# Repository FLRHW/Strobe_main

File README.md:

<h1 align="center">Main board</h1>

<p align="center" width="100%">
  
</p>

***

<p align="center">
  
&nbsp; &nbsp; &nbsp; &nbsp;
  
</p>

***

# **1 kV strobe - Intro**
Since my teenage years I spend a great chunk of my spare time on hobby electronics. Back then, much of that time was to build FM transmitters, audio amplifiers and strobe lights. I was always pushing my builds as much as I could, (i.e., extracting pressurised smoke from capacitors!) as an attempt to make the flashes ever brighter. It was somewhat challenging given the limited experience and resources I had at the time, but a lot of fun nonetheless.
Life went on, priorities changed and for a long time I did not "play" with strobe lights... until recently, after I saw a large XOP-15 bulb for sale and, well, nostalgy happened.

While defining the project scope, I had to decide if I'd use the good old Xenon bulb or move to LEDs, as these have greatly evolved and are ubiquitous nowadays, making their way to commercial strobes (https://www.martin.com/en/products/atomic-3000-led). I have decided to stick to vintage tech, as in my mind this would bring more interesting power electronics challenges due to high voltages and high peak currents required when the lamp is ionised.

So that's what this repo contains: a Xenon-based strobe light, aiming to drive a XOP-15 bulb with up to 1 kV, while controlling the duration and frequency of pulses.

## Project overview
This repository contains KiCad v9 design files for the main board of a Xenon-based strobe light system.
The system is divided into three separate modules:

- Main board. This board drives the Xenon bulb, generating the trigger pulse and actively interrupting the discharge according to the required pulse width. The latest STM32 source code is kept on a separate repository:  
https://github.com/FLRHW/Strobe_main_source  

- HMI board. This is the user interface, to capture desired operating conditions (bus voltage, pulse width and pulse frequency). That board is covered on a separate repository:  
https://github.com/FLRHW/Strobe_HMI  

- Power supply. This is to produce an adjustable DC supply and to realise that I intend to eventually design an AC-mains powered converter, including a PFC circuit. As an interim solution, off-the-shelf boost converter modules are used: two such modules are connected in series, each providing up to 450 V output while supplied by 12 V batteries. As a side project, the boost modules have been reverse engineered with the aim to modify them from non-isolated to isolated. This work is covered under the following repos:
https://github.com/FLRHW/StepUp_module_12to450V  
https://github.com/FLRHW/Isolated_12to450V.

## Design targets
DC bus voltage: 400 V to 1000 V  
Flash rate: 0.1 Hz to 200 Hz  
Pulse duration: 20 μs to 10 ms  

Please note that the above parameters are only the limits encoded in the software. This design relies on storing energy on a capacitor bank to then discharge it into the bulb, so, even though the limit in software for the pulse duration is 50 % of the period, long durations might be unachievable. The duration strongly depends on the lamp, capacitor bank and bus voltage. As an example, with the XOP-15 and a 400 uF bank charged to 700 V, the discharge current reaches 450 A and the bank voltage collapses in less than 1 ms. Additionally, the HV power supply will determine how fast the capacitor bank is recharged, limiting the flash rate and/or pulse duration.

## Intended use
This repository is intended for:
* Educational use and study of the circuit;
* Integration into hobby or research projects.

## License
The design files and documentation in this repository are released under the CERN Open Hardware Licence v2 – Permissive (CERN‑OHL‑P‑2.0). SPDX identifier: CERN-OHL-P-2.0 See the LICENSE file for the full legal text and conditions.
In short and non‑legal terms, you are free to use, modify, manufacture, and distribute hardware based on these files, provided you respect attribution requirements and the terms in the license.

## Trademarks and third‑party rights
All product names, logos, and brands eventually mentioned are the property of their respective owners and are not included or licensed here.
Any reference to third‑party marks is purely descriptive and does not imply endorsement or affiliation.

## Safety and disclaimer
* The author takes no responsibility for any injury, death or damage arising from the use, direct or indirect, of the design or otherwise any information from this repository
* You shall not build this or any prototype based on this design unless you are absolutely sure of your abilities dealing with this type of circuit
* High voltage can cause injury, death, or damage to equipment. Ensure appropriate protections and testing procedures are followed
* The design is provided as is, with no warranty of any kind
* Users are responsible for checking any patent, copyright, or regulatory constraints that may apply to their own use

## Known issues / improvement potentials
- To be updated once prototype is tested

***

## DIRECTORY STRUCTURE
    │
    ├─ Computations       # Misc calculations
    ├─ HTML               # HTML files for generated webpage
    ├─ Images             # Pictures and renders
    │
    ├─ kibot_resources    # External resources for KiBot
    │  ├─ colors          # Color theme for KiCad
    │  ├─ fonts           # Fonts used in the project
    │  ├─ scripts         # External scripts used with KiBot
    │  └─ templates       # Templates for KiBot generated reports
    │
    ├─ kibot_yaml         # KiBot YAML config files
    ├─ KiRI               # KiRI (PCB diff viewer) files
    │
    ├─ lib                # KiCad footprint and symbol libraries
    │  ├─ 3d_models       # Component 3D models
    │  ├─ lib_fp          # Footprint libraries
    │  └─ lib_sym         # Symbol libraries
    │
    ├─ Logos              # Logos
    │
    ├─ Manufacturing      # Assembly and fabrication documents
    │  ├─ Assembly        # Assembly documents (BoM, pos, notes)
    │  │
    │  └─ Fabrication     # Fabrication documents (ZIP, notes)
    │     ├─ Drill Tables # CSV drill tables
    │     └─ Gerbers      # Gerbers
    │
    ├─ Report             # Reports for ERC/DRC
    ├─ Schematic          # PDF of schematic
    ├─ Templates          # Title block templates
    ├─ Testing
    │  └─ Testpoints      # Testpoints tables      
    │
    └─ Variants           # Outputs for assembly variants

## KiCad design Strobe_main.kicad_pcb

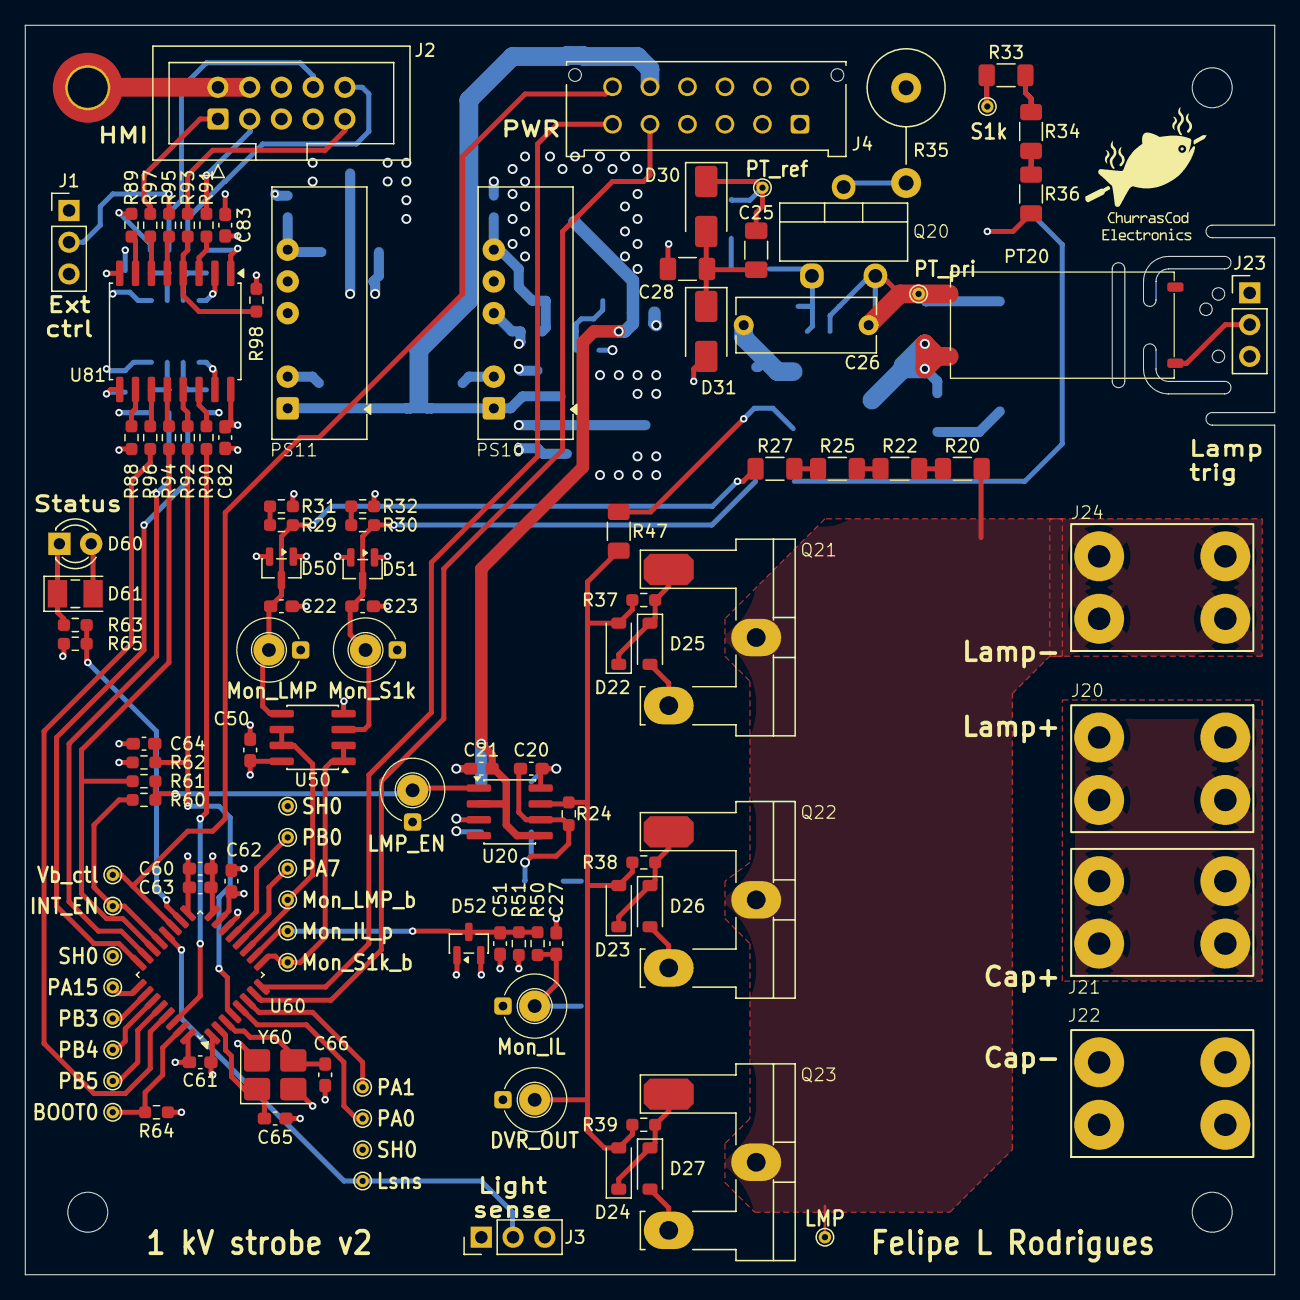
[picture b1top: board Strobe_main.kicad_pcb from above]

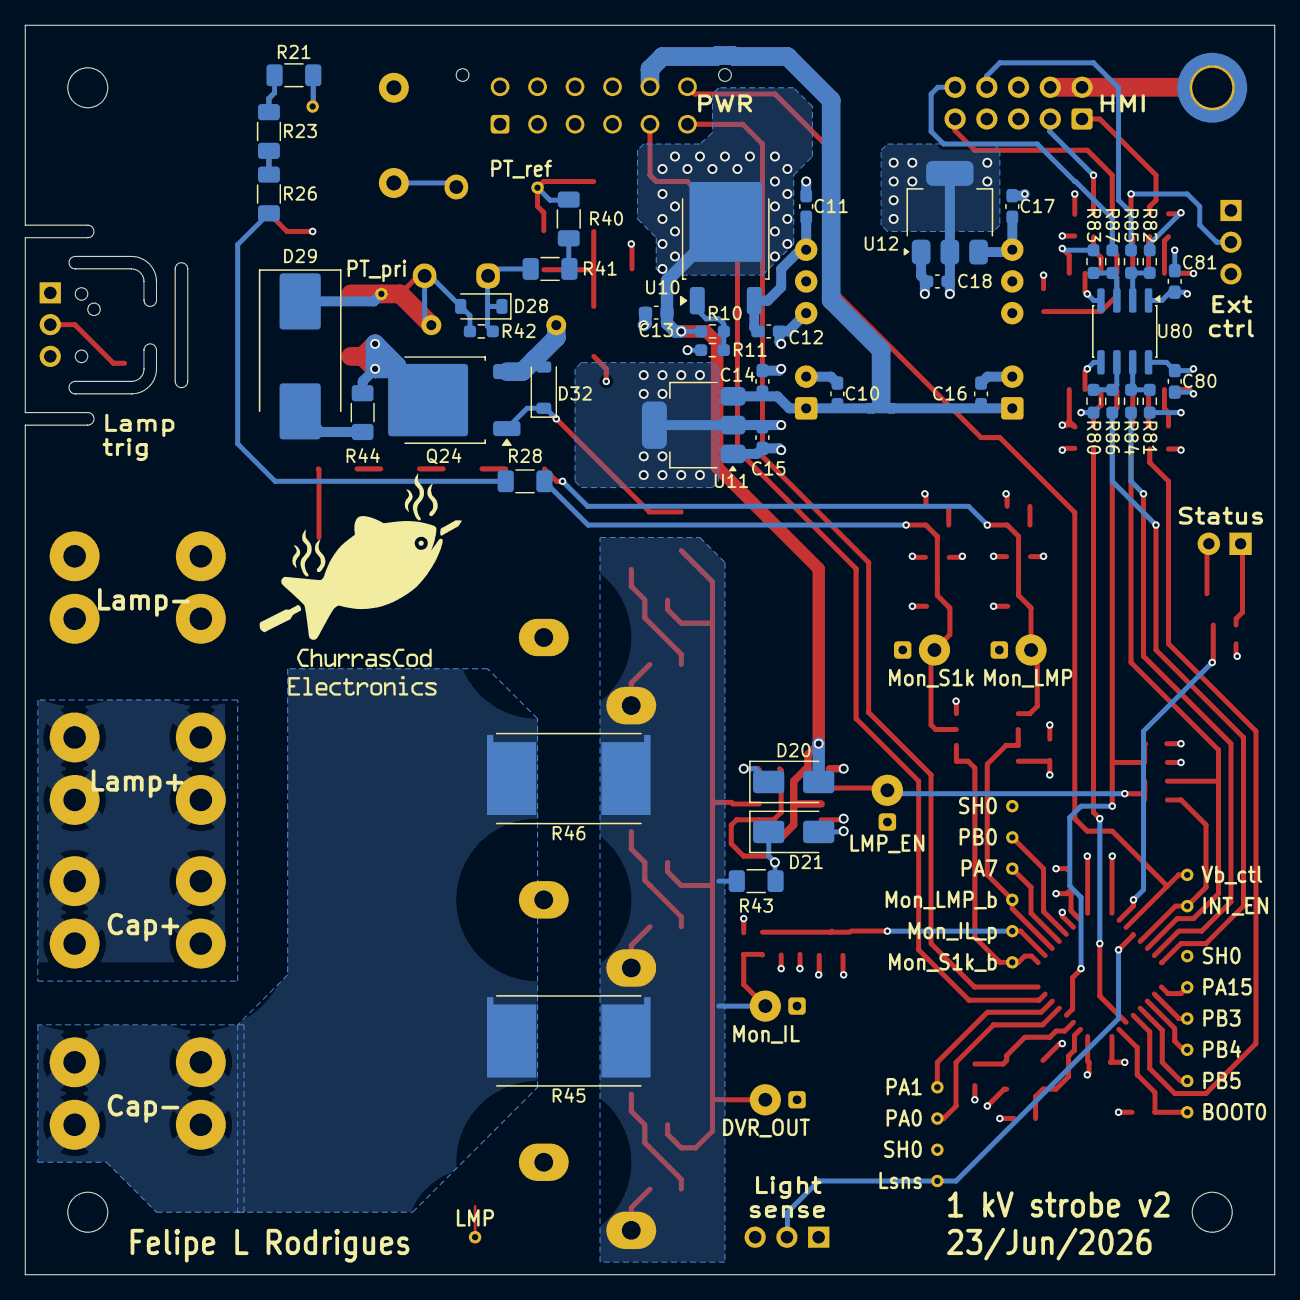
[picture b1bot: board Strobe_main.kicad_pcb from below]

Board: 4 copper layers, 100.0 x 100.0 mm, 165 parts (42 on the bottom side), 89 nets.

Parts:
C10, C11, C13, C14, C16, C17, C60: 1u; C_0603_1608Metric_Pad1.08x0.95mm_HandSolder
C12, C15, C18, C20, C21, C22, C23, C27, C50, C61, C62, C63, C64, C80, C81, C82, C83: 100n; C_0603_1608Metric_Pad1.08x0.95mm_HandSolder
C25, C28: 100n; C_1206_3216Metric_Pad1.33x1.80mm_HandSolder
C26: 47n; C_Rect_L11.0mm_W4.2mm_P10.00mm_MKT
C51: 4n7; C_0603_1608Metric_Pad1.08x0.95mm_HandSolder
C65, C66: 22p; C_0603_1608Metric_Pad1.08x0.95mm_HandSolder
D20, D21: B360; D_SMA
D22, D23, D24: 1N4148; D_SOD-123
D25, D26, D27, D28, D32: 20 V; D_SOD-123
D29: S15M; D_SMC_Handsoldering
D30, D31: 1SMA5953B; D_SMA
D50, D51, D52: BAV199; SOT-23
D60: LED; LED_D3.0mm
D61: LED; LED_PLCC-2_3x2mm_KA
H1, H3, H4: MountingHole; MountingHole_3.2mm_M3
H2: MountingHole_Pad; MountingHole_3.2mm_M3_DIN965_Pad_TopBottom
H20, H21, H22: MountingHole; Hole_1.0mm
J1, J3, J23: Header; PinHeader_1x03_P2.54mm_Vertical
J2: ZHOURI DC3; IDC-Header_2x05_P2.54mm_Vertical
J4: Molex 430451227; Molex_Micro-Fit_3.0_43045-1212_2x06_P3.00mm_Vertical
J20, J21, J22, J24: T44007
PS10: B0524S-2W; DCDC_converter_THT_BxxxxS-2W
PS11: B0505S-2W; DCDC_converter_THT_BxxxxS-2W
PT20: ZS1052-S_HT
Q20: MPF3N150; To-220_staggered_3
Q21, Q22, Q23: IXYH55N120; TO-247_mixed_pads_vert
Q24: MDT7N65; TO-252-2
R10: 470; R_0603_1608Metric_Pad0.98x0.95mm_HandSolder
R11: 6k8; R_0603_1608Metric_Pad0.98x0.95mm_HandSolder
R20, R21, R22, R23, R25, R26, R27, R28: 510k; R_1206_3216Metric_Pad1.30x1.75mm_HandSolder
R24: 15k; R_0603_1608Metric_Pad0.98x0.95mm_HandSolder
R29, R30, R31, R32: 3k3; R_0603_1608Metric_Pad0.98x0.95mm_HandSolder
R33, R34, R36: 330k; R_1206_3216Metric_Pad1.30x1.75mm_HandSolder
R35: 100k; R_Axial_DIN0617_L17.0mm_D6.0mm_P7.62mm_Vertical
R37, R38, R39: 91R; R_0603_1608Metric_Pad0.98x0.95mm_HandSolder
R40, R41: 110k; R_1206_3216Metric_Pad1.30x1.75mm_HandSolder
R42: 100k; R_0603_1608Metric_Pad0.98x0.95mm_HandSolder
R43: 22R; R_1206_3216Metric_Pad1.30x1.75mm_HandSolder
R44: 1R; R_1206_3216Metric_Pad1.30x1.75mm_HandSolder
R45, R46: 20m; R_Shunt_Vishay_WSR2_WSR3_KelvinConnection
R47: 10R; R_1206_3216Metric_Pad1.30x1.75mm_HandSolder
R50, R51: 220; R_0603_1608Metric_Pad0.98x0.95mm_HandSolder
R60, R61, R84, R85, R86, R87, R90, R91, R92, R93, R94, R95, R96, R97: 0R; R_0603_1608Metric_Pad0.98x0.95mm_HandSolder
R62, R64, R65, R88, R89, R98: 10k; R_0603_1608Metric_Pad0.98x0.95mm_HandSolder
R63: 1k; R_0603_1608Metric_Pad0.98x0.95mm_HandSolder
R80, R81, R82, R83: 4k7; R_0603_1608Metric_Pad0.98x0.95mm_HandSolder
TP20, TP21, TP22, TP23, TP28: Testpoint_osc_probe; Testpoint_osc_no_lead
TP24, TP25, TP26, TP27, TP60, TP61, TP62, TP63, TP64, TP65, TP66, TP67, TP68, TP69, TP70, TP71, TP72, TP73, TP74, TP75, TP76, TP77: TestPoint; TestPoint_THTPad_D1.0mm_Drill0.5mm
U10: LM217MDT; TO-252-2
U11, U12: NCP1117IST33T3G; SOT-223-3_TabPin2
U20: IRS2184; SOIC-8_3.9x4.9mm_P1.27mm
U50: TSV912IDT; SOIC-8_3.9x4.9mm_P1.27mm
U60: STM32G431K8Tx; LQFP-32_7x7mm_P0.8mm
U80: ISO1541; SOIC-8_3.9x4.9mm_P1.27mm
U81: ISO6741; SOIC-16W_7.5x10.3mm_P1.27mm
Y60: 20 MHz; Crystal_SMD_3225-4Pin_3.2x2.5mm_HandSoldering

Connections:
/Block Diagram/Ext_EN: J1.2, R95.2
/Block Diagram/GND: C17.2, C18.2, C81.2, C83.2, J1.1, J2.5, J2.7, PS11.4 (-Vout), R98.2, U12.1 (GND), U80.4 (GND1), U81.2 (GND1), U81.8 (GND1)
/Block Diagram/Lamp driver/DRV_OUT: D22.2 (A), D23.2 (A), D24.2 (A), R24.2, R37.1, R38.1, R39.1, R47.1, TP20.1 (Sig), U20.7 (HO)
/Block Diagram/Lamp driver/DRV_RET: C20.2, D21.1 (K), R24.1, R43.2, U20.6 (VS)
/Block Diagram/Lamp driver/G_L_D1: D22.1 (K), D25.1 (K), Q21.1 (G), R37.2
/Block Diagram/Lamp driver/G_L_D2: D23.1 (K), D26.1 (K), Q22.1 (G), R38.2
/Block Diagram/Lamp driver/G_L_D3: D24.1 (K), D27.1 (K), Q23.1 (G), R39.2
/Block Diagram/Lamp driver/G_TP_DRV: D32.1 (K), Q24.1 (G), R47.2
/Block Diagram/Lamp driver/G_TP_REF: D28.1 (K), Q20.1 (G), R41.2, R42.1
/Block Diagram/Lamp driver/LMP: J24.1, Q21.2 (C), Q22.2 (C), Q23.2 (C), R20.2, TP25.1
/Block Diagram/Lamp driver/LMP_EN: R60.2, R61.2, TP21.1 (Sig), U20.1 (IN)
/Block Diagram/Lamp driver/Mon_IL: C27.1, D25.2 (A), D26.2 (A), D27.2 (A), Q21.3 (E), Q22.3 (E), Q23.3 (E), R43.1, R45.1, R46.1, R50.1, TP28.1 (Sig)
/Block Diagram/Lamp driver/Mon_LMP: C22.1, D50.3 (K), R27.1, R29.2, TP22.1 (Sig), U50.5 (+)
/Block Diagram/Lamp driver/Mon_S1k: C23.1, D51.3 (K), R28.1, R30.2, TP23.1 (Sig), U50.3 (+)
/Block Diagram/Lamp driver/REF_M: C25.2, C28.1, D30.2 (A), D31.1 (K)
/Block Diagram/Lamp driver/TP_COM: PT20.1 (C), Q24.2 (D), R44.1
/Block Diagram/Lamp driver/TP_DRV_COL: Q20.2 (D), R35.2
/Block Diagram/Lamp driver/TP_INT: D29.2 (A), R44.2
/Block Diagram/Lamp driver/TP_PRI: C26.1, D28.2 (A), D29.1 (K), PT20.2, Q20.3 (S), R42.2, TP27.1
/Block Diagram/Lamp driver/TP_REF: C25.1, D30.1 (K), R36.1, R40.1, TP26.1
/Block Diagram/Lamp driver/TP_RM: R40.2, R41.1
/Block Diagram/Lamp driver/TRIG: J23.2, PT20.4 (S)
/Block Diagram/Lamp driver/VBS: C20.1, D20.1 (K), U20.8 (VB)
/Block Diagram/Light_sns: J3.2, TP71.1, U60.20 (PA10)
/Block Diagram/MCU/BOOT0: R64.1, TP73.1, U60.31 (PB8)
/Block Diagram/MCU/HV_EXT_EN: R61.1, R94.1, U60.22 (PA12)
/Block Diagram/MCU/HV_NRST: C64.1, R62.2, R92.1, U60.4 (PG10)
/Block Diagram/MCU/HV_RX: R90.1, U60.30 (PB7)
/Block Diagram/MCU/HV_SWDCLK: R86.1, U60.24 (PA14)
/Block Diagram/MCU/HV_SWDIO: R84.1, U60.23 (PA13)
/Block Diagram/MCU/HV_TX: R96.1, U60.29 (PB6)
/Block Diagram/MCU/INT_EN: R60.1, TP72.1, U60.21 (PA11)
/Block Diagram/MCU/Mon_IL_prot: C51.1, D52.3 (K), R50.2, R51.2, TP64.1, U60.10 (PA5)
/Block Diagram/MCU/Mon_LMP_buf: TP66.1, U50.6 (-), U50.7, U60.11 (PA6)
/Block Diagram/MCU/Mon_S1k_buf: TP62.1, U50.1, U50.2 (-), U60.9 (PA4)
/Block Diagram/MCU/ST_LED: R63.2, R65.1, U60.18 (PA8)
/Block Diagram/MCU/SUP_RX: J4.6, U60.8 (PA3)
/Block Diagram/MCU/SUP_TX: J4.5, U60.7 (PA2)
/Block Diagram/Optical isolation/LV_NRST: J2.9, R93.2
/Block Diagram/Optical isolation/LV_RX: J2.1, R97.2
/Block Diagram/Optical isolation/LV_SWDCLK: J2.10, R87.2
/Block Diagram/Optical isolation/LV_SWDIO: J2.8, R85.2
/Block Diagram/Optical isolation/LV_TX: J2.3, R91.2
/Block Diagram/Power supply/SH24: C11.1, C12.1, PS10.6 (+Vout), U10.3 (VI)
/Block Diagram/Power supply/SL5: C17.1, PS11.6 (+Vout), U12.3 (VI)
/Block Diagram/S1k: J4.7, J20.1, J21.1, R21.2, R33.1, R35.1, TP24.1
/Block Diagram/SH0: C10.2, C11.2, C12.2, C13.2, C14.2, C15.2, C16.2, C21.2, C22.2, C23.2, C26.2, C27.2, C28.2, C50.2, C51.2, C60.2, C61.2, C62.2, C63.2, C64.2, C65.2, C66.2, C80.2, C82.2, D21.2 (A), D31.2 (A), D32.2 (A), D50.1 (K), D51.1 (K), D52.1 (K), J3.3, J4.4, J4.10, J22.1, PS10.2 (-Vin), PS10.4 (-Vout), PS11.2 (-Vin), Q24.3 (S), R11.2, R31.1, R32.1, R45.2, R46.2, R51.1, R64.2, R65.2, TP20.2 (Ref), TP21.2 (Ref), TP22.2 (Ref), TP23.2 (Ref), TP28.2 (Ref), TP75.1, TP76.1, TP77.1, U11.1 (GND), U20.3 (COM), U50.4 (V-), U60.14 (VSSA), U60.16 (VSS), U60.32 (VSS), U80.5 (GND2), U81.9 (GND2), U81.15 (GND2), Y60.2 (G), Y60.4 (G)
/Block Diagram/SH3: C15.1, C50.1, C60.1, C61.1, C62.1, C63.1, C80.1, C82.1, D50.2 (A), D51.2 (A), D52.2 (A), D60.2 (A), D61.2 (A), J3.1, R62.1, R80.1, R81.1, R88.1, U11.2 (VO), U50.8 (V+), U60.1 (VDD), U60.15 (VDDA), U60.17 (VDD), U80.8 (VCC2), U81.16 (V_{CC2})
/Block Diagram/SH5: C10.1, C14.1, C16.1, J4.11, PS10.1 (+Vin), PS11.1 (+Vin), U11.3 (VI)
/Block Diagram/SH20: C13.1, C21.1, D20.2 (A), R10.1, U10.2 (VO), U20.2 (~SD), U20.5 (VCC)
/Block Diagram/SL3: C18.1, C81.1, C83.1, J1.3, J2.6, R82.1, R83.1, R89.1, U12.2 (VO), U80.1 (VCC1), U81.1 (V_{CC1})
/Block Diagram/Vbus_ctrl: J4.12, TP70.1, U60.19 (PA9)
Earth: H2.1, J2.2, J2.4
unnamed: D60.1 (K), D61.1 (K), R63.1
unnamed: R20.1, R22.2
unnamed: R21.1, R23.2
unnamed: R22.1, R25.2
unnamed: R23.1, R26.2
unnamed: R25.1, R27.2
unnamed: R26.1, R28.2
unnamed: R29.1, R31.2
unnamed: R30.1, R32.2
unnamed: R33.2, R34.1
unnamed: R34.2, R36.2
unnamed: R10.2, R11.1, U10.1 (ADJ)
unnamed: TP60.1, U60.5 (PA0)
unnamed: TP61.1, U60.6 (PA1)
unnamed: TP68.1, U60.12 (PA7)
unnamed: TP74.1, U60.25 (PA15)
unnamed: TP63.1, U60.13 (PB0)
unnamed: TP65.1, U60.26 (PB3)
unnamed: TP67.1, U60.27 (PB4)
unnamed: TP69.1, U60.28 (PB5)
unnamed: C65.1, U60.2 (PF0), Y60.1
unnamed: C66.1, U60.3 (PF1), Y60.3
unnamed: R83.2, R87.1, U80.3 (SCL1)
unnamed: R80.2, R86.2, U80.6 (SCL2)
unnamed: R82.2, R85.1, U80.2 (SDA1)
unnamed: R81.2, R84.2, U80.7 (SDA2)
unnamed: R89.2, U81.7 (EN1)
unnamed: R88.2, U81.10 (EN2)
unnamed: R91.1, U81.3 (INA)
unnamed: R93.1, R98.1, U81.4 (INB)
unnamed: R95.1, U81.5 (INC)
unnamed: R96.2, U81.11 (IND)
unnamed: R90.2, U81.14 (OUTA)
unnamed: R92.2, U81.13 (OUTB)
unnamed: R94.2, U81.12 (OUTC)
unnamed: R97.1, U81.6 (OUTD)

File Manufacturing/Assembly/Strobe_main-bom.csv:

Row,Quantity Per PCB,References,Value,Datasheet,Footprint,Description,Manufacturer,Manufacturer Part Number,Supplier Part Number
1,2,C65 C66,22p,~,C_0603_1608Metric_Pad1.08x0.95mm_HandSolder,Unpolarized capacitor,Generic,,
2,2,C22 C23,1n,~,C_0603_1608Metric_Pad1.08x0.95mm_HandSolder,Unpolarized capacitor,Generic,,
3,1,C51,4n7,~,C_0603_1608Metric_Pad1.08x0.95mm_HandSolder,Unpolarized capacitor,Generic,,
4,1,C26,47n,~,C_Rect_L11.0mm_W4.2mm_P10.00mm_MKT,Unpolarized capacitor,Generic,,
5,17,C12 C15 C18 C20 C21 C25 C27 C28 C50 C61 C62 C63 C64 C80 C81 C82 C83,100n,~,C_0603_1608Metric_Pad1.08x0.95mm_HandSolder,Unpolarized capacitor,Generic,,
6,7,C10 C11 C13 C14 C16 C17 C60,1u,~,C_0603_1608Metric_Pad1.08x0.95mm_HandSolder,Unpolarized capacitor,Generic,,
7,3,D22 D23 D24,1N4148,~,D_SOD-123,Diode,DIODES,1N4148W-7-F,
8,2,D30 D31,1SMA5953B,https://diotec.com/tl_files/diotec/files/pdf/datasheets/z1sma1.pdf,D_SMA,"1000mW Zener Diode, SMA(DO-214AC)",Jingdao Microelectronics,1SMA5953B,
9,5,D25 D26 D27 D28 D32,20 V,~,D_SOD-123,Zener diode,HXY MOSFET,BZT52C20,
10,2,D20 D21,B360,~,D_SMA,Schottky diode,DIODES,B360A-13-F,
11,3,D50 D51 D52,BAV199,https://assets.nexperia.com/documents/data-sheet/BAV99_SER.pdf,SOT-23,"BAV99 High-speed switching diodes, SOT-23",onsemi,BAV199LT1G,
12,2,D60 D61,LED,~,LED_D3.0mm,Light emitting diode,Generic,,
13,1,D29,S15M,~,D_SMC_Handsoldering,Diode,LGE,S15M,
14,9,J1 J2 J3 J4 J20 J21 J22 J23 J24,Header,~,PinHeader_1x03_P2.54mm_Vertical,"Generic connector, single row, 01x03, script generated Generic connector, double row, 02x05, odd/even pin numbering scheme (row 1 odd numbers, row 2 even numbers), script generated (kicad-library-utils/schlib/autogen/connector/) Generic connector, double row, 02x06, top/bottom pin numbering scheme (row 1: 1...pins_per_row, row2: pins_per_row+1 ... num_pins), script generated (kicad-library-utils/schlib/autogen/connector/) Generic screw terminal, single row, 01x01, script generated (kicad-library-utils/schlib/autogen/connector/)",Generic ZHOURI Molex XFCN,DC3-2.54-10PAS 430451227 T44007,
15,1,PS11,B0505S-2W,https://www.lcsc.com/datasheet/C5198437.pdf?spm=wm.fly.bg.0.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,DCDC_converter_THT_BxxxxS-2W,,Evisun,B0505S-2W,
16,1,PS10,B0524S-2W,https://www.lcsc.com/datasheet/C5198437.pdf?spm=wm.fly.bg.0.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,DCDC_converter_THT_BxxxxS-2W,,Evisun,B0524S-2W,
17,1,PT20,ZS1052-S_HT,,ZS1052-S_HT,,Excelitas Technologies,ZS1052-S_HT,
18,3,Q21 Q22 Q23,IXYH55N120,~,TO-247_mixed_pads_vert,"N-IGBT transistor, gate/collector/emitter",IXYS,IXYH55N120,
19,1,Q24,MDT7N65,,TO-252-2,,Minos,MDT7N65,
20,1,Q20,MPF3N150,https://media.digikey.com/pdf/Data%20Sheets/Fairchild%20PDFs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,To-220_staggered_3,"30A Id, 50V Vds, N-Channel Power MOSFET, TO-220",Minos,MPF3N150,
21,13,R60 R84 R85 R86 R87 R90 R91 R92 R93 R94 R95 R96 R97,0R,~,R_0603_1608Metric_Pad0.98x0.95mm_HandSolder,Resistor,Generic,,
22,2,R45 R46,20m,~,R_Shunt_Vishay_WSR2_WSR3_KelvinConnection,Resistor,Vishay Intertech,WSR3R0200FEA,
23,1,R44,1R,~,R_1206_3216Metric_Pad1.30x1.75mm_HandSolder,Resistor,Generic,,
24,1,R47,10R,~,R_1206_3216Metric_Pad1.30x1.75mm_HandSolder,Resistor,Generic,,
25,1,R43,22R,~,R_1206_3216Metric_Pad1.30x1.75mm_HandSolder,Resistor,Generic,,
26,3,R37 R38 R39,91R,~,R_0603_1608Metric_Pad0.98x0.95mm_HandSolder,Resistor,Generic,,
27,2,R50 R51,220,~,R_0603_1608Metric_Pad0.98x0.95mm_HandSolder,Resistor,Generic,,
28,1,R10,470,~,R_0603_1608Metric_Pad0.98x0.95mm_HandSolder,Resistor,Generic,,
29,1,R63,1k,~,R_0603_1608Metric_Pad0.98x0.95mm_HandSolder,Resistor,Generic,,
30,4,R29 R30 R31 R32,3k3,~,R_0603_1608Metric_Pad0.98x0.95mm_HandSolder,Resistor,Generic,,
31,4,R80 R81 R82 R83,4k7,~,R_0603_1608Metric_Pad0.98x0.95mm_HandSolder,Resistor,Generic,,
32,1,R11,6k8,~,R_0603_1608Metric_Pad0.98x0.95mm_HandSolder,Resistor,Generic,,
33,6,R62 R64 R65 R88 R89 R98,10k,~,R_0603_1608Metric_Pad0.98x0.95mm_HandSolder,Resistor,Generic,,
34,1,R24,15k,~,R_0603_1608Metric_Pad0.98x0.95mm_HandSolder,Resistor,Generic,,
35,2,R35 R42,100k,~,R_Axial_DIN0617_L17.0mm_D6.0mm_P7.62mm_Vertical,Resistor,Generic,,
36,2,R40 R41,110k,~,R_1206_3216Metric_Pad1.30x1.75mm_HandSolder,Resistor,Generic,,
37,3,R33 R34 R36,330k,~,R_1206_3216Metric_Pad1.30x1.75mm_HandSolder,Resistor,Generic,,
38,8,R20 R21 R22 R23 R25 R26 R27 R28,510k,~,R_1206_3216Metric_Pad1.30x1.75mm_HandSolder,Resistor,Generic,,
39,1,U20,IRS2184,https://www.infineon.com/dgdl/irs2184.pdf?fileId=5546d462533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,SOIC-8_3.9x4.9mm_P1.27mm,"Half-Bridge Driver, 600V, 1.4/1.8A, PDIP-8/SOIC-8",Infineon,IRS2184,
40,1,U80,ISO1541,http://www.ti.com/lit/ds/symlink/iso1541.pdf,SOIC-8_3.9x4.9mm_P1.27mm,"I2C Isolator, 2.5 kVrms, Unidirectional Clock, Bidirectional data, SOIC-8",Texas Instruments,ISO1541DR,
41,1,U81,ISO6741,https://www.ti.com/lit/ds/symlink/iso6741.pdf,SOIC-16W_7.5x10.3mm_P1.27mm,"General-purpose, quad-channel, 3/1 digital isolator",Texas Instruments,ISO6741DWR,
42,1,U10,LM217MDT,http://www.ti.com/lit/ds/snvs774n/snvs774n.pdf,TO-252-2,"1.5A 35V Adjustable Linear Regulator, TO-252",ST,LM217MDT,
43,2,U11 U12,NCP1117IST33T3G,https://www.lcsc.com/datasheet/C114733.pdf?spm=wm.fly.bg.6.p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,SOT-223-3_TabPin2,"1A Low Dropout regulator, positive, 3.3V fixed output, SOT-223",Onsemi,NCP1117IST33T3G,
44,1,U60,STM32G431K8Tx,https://www.st.com/resource/en/datasheet/stm32g431k8.pdf,LQFP-32_7x7mm_P0.8mm,"STMicroelectronics Arm Cortex-M4 MCU, 64KB flash, 32KB RAM, 170 MHz, 1.71-3.6V, 26 GPIO, LQFP32",STMicroelectronics,STM32G431K8T6,
45,1,U50,TSV912IDT,www.st.com/resource/en/datasheet/tsv911.pdf,SOIC-8_3.9x4.9mm_P1.27mm,"Dual rail-to-rail input/output 8 MHz operational amplifiers, SOIC-8",ST,TSV912IDT,
46,1,Y60,20 MHz,~,Crystal_SMD_3225-4Pin_3.2x2.5mm_HandSoldering,"Four pin crystal, GND on pins 2 and 4, small symbol",Generic,,

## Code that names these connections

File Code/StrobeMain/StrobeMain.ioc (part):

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Mcu.Name=STM32G431K(6-8-B)Tx
Mcu.Package=LQFP32
Mcu.UserName=STM32G431K8Tx
PA0.GPIOParameters=GPIO_Label
PA0.GPIO_Label=U_SH1000
PA0.Mode=IN1-Single-Ended
PA0.Signal=ADC1_IN1
PA1.GPIOParameters=GPIO_Label
PA1.GPIO_Label=U_SH240
PA1.Mode=IN2-Single-Ended
PA1.Signal=ADC1_IN2
PA11.GPIOParameters=GPIO_Label
PA11.GPIO_Label=LAMP_EN
PA11.Signal=GPIO_Output
PA12.GPIOParameters=GPIO_Label
PA12.GPIO_Label=TP516
PA12.Signal=GPIO_Output
PA13.Mode=Serial_Wire
PA13.Signal=SYS_JTMS-SWDIO
PA14.Mode=Serial_Wire
PA14.Signal=SYS_JTCK-SWCLK
PA15.Signal=GPIO_Output
PA2.GPIOParameters=GPIO_Label
PA2.GPIO_Label=I_SH240
PA2.Mode=IN3-Single-Ended
PA2.Signal=ADC1_IN3
PA3.GPIOParameters=GPIO_Label
PA3.GPIO_Label=I_SH1000
PA3.Mode=IN4-Single-Ended
PA3.Signal=ADC1_IN4
PA4.GPIOParameters=GPIO_Label
PA4.GPIO_Label=U_L
PA4.Mode=IN17-Single-Ended
PA4.Signal=ADC2_IN17
PA5.GPIOParameters=GPIO_Label
PA5.GPIO_Label=I_P
PA5.Mode=IN13-Single-Ended
PA5.Signal=ADC2_IN13
PA6.GPIOParameters=GPIO_Label
PA6.GPIO_Label=U_C
PA6.Mode=IN3-Single-Ended
PA6.Signal=ADC2_IN3
PA7.GPIOParameters=GPIO_Label
PA7.GPIO_Label=TP511
PA7.Signal=GPIO_Output
PA8.GPIOParameters=GPIO_Label
PA8.GPIO_Label=ST_LED
PA8.Signal=GPIO_Output
PB0.GPIOParameters=GPIO_Label
PB0.GPIO_Label=TP506
PB0.Signal=GPIO_Output
PB3.GPIOParameters=GPIO_Label
PB3.GPIO_Label=TP508
PB3.Signal=GPIO_Output
PB4.GPIOParameters=GPIO_Label
PB4.GPIO_Label=TP510
PB4.Signal=GPIO_Output
PB5.GPIOParameters=GPIO_Label
PB5.GPIO_Label=TP512
PB5.Signal=GPIO_Output
PB6.GPIOParameters=GPIO_Label
PB6.GPIO_Label=HV_TX
PB6.Mode=Asynchronous
PB6.Signal=USART1_TX
PB7.GPIOParameters=GPIO_Label
PB7.GPIO_Label=HV_RX
PB7.Mode=Asynchronous
PB7.Signal=USART1_RX
PF0-OSC_IN.Mode=HSE-External-Oscillator
PF0-OSC_IN.Signal=RCC_OSC_IN
PF1-OSC_OUT.Mode=HSE-External-Oscillator
PF1-OSC_OUT.Signal=RCC_OSC_OUT
RCC.HSE_VALUE=20000000
RCC.SYSCLKFreq_VALUE=150000000
RCC.SYSCLKSource=RCC_SYSCLKSOURCE_PLLCLK
board=custom

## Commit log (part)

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2026-02-18 Sch copy in progress
2026-02-18 Update Outputs
2026-02-18 Deleting old sch files
2026-02-19 Reworked sheet titles
2026-02-19 Reworked sheet titles and changelog
2026-02-19 reverted to draft
2026-02-19 Added PCB
2026-02-19 Added some libraries to project folder
2026-02-19 added more 3d models and paths
2026-02-19 forcing workflow
2026-02-19 added missing 3d step files
2026-02-19 Added z offset to DCDC modules
2026-02-20 Started update of mfg docs
2026-02-20 Updating mfg docs
2026-02-20 Updating sheet size on yaml
2026-02-20 added 3d model for J501
2026-02-20 Updated fab layer
2026-02-20 added firmware
2026-04-08 Setting up repo on another machine
2026-04-08 Trigger ci
2026-04-08 Workflow file updated
2026-04-09 Readme updated
2026-04-10 updating BOM info
2026-04-11 mfg docs updated
2026-04-11 Checked. Preparing release
2026-04-11 Update CHANGELOG
2026-04-11 Update Outputs (release)
2026-05-22 Added some simulation files and to do list on changelog
2026-05-28 Updated simulation files and readme
2026-05-28 Preparing release
2026-06-02 Sch update in progress
2026-06-02 Fixed CI file
2026-06-02 Sch update in progres
2026-06-03 Sch update complete, ERC OK
2026-06-05 Placement started
2026-06-06 Placement 50%
2026-06-07 Updated pulse transofrmer circuit
2026-06-08 Placement updates
2026-06-09 New placement strategy
2026-06-09 TP placement candidate 90%
2026-06-11 Updated some clearance rules
2026-06-11 Placement complplete, feasibility routing complete
2026-06-12 MCU routed
2026-06-12 Routing complete, silk to do, vias to check, one footprint to update
2026-06-13 Reannotated, silk done, missing some 3D models
2026-06-14 3D models added
2026-06-14 Copied libraries
2026-06-14 Forcing CI
2026-06-14 Updated paths to 3D models
2026-06-14 Testing paths
2026-06-14 Testing path 2
2026-06-14 Paths fixed
2026-06-17 Addupdated edge cuts near trigger output
2026-06-18 Updating mfg layers
2026-06-22 Changed to checked, updated fab pdf yaml
2026-06-23 Updated thermal reliefs and fiing holes positions
2026-06-23 Preparing release from dev2
2026-06-23 Fixed small DFM warnings from JLCPCB
